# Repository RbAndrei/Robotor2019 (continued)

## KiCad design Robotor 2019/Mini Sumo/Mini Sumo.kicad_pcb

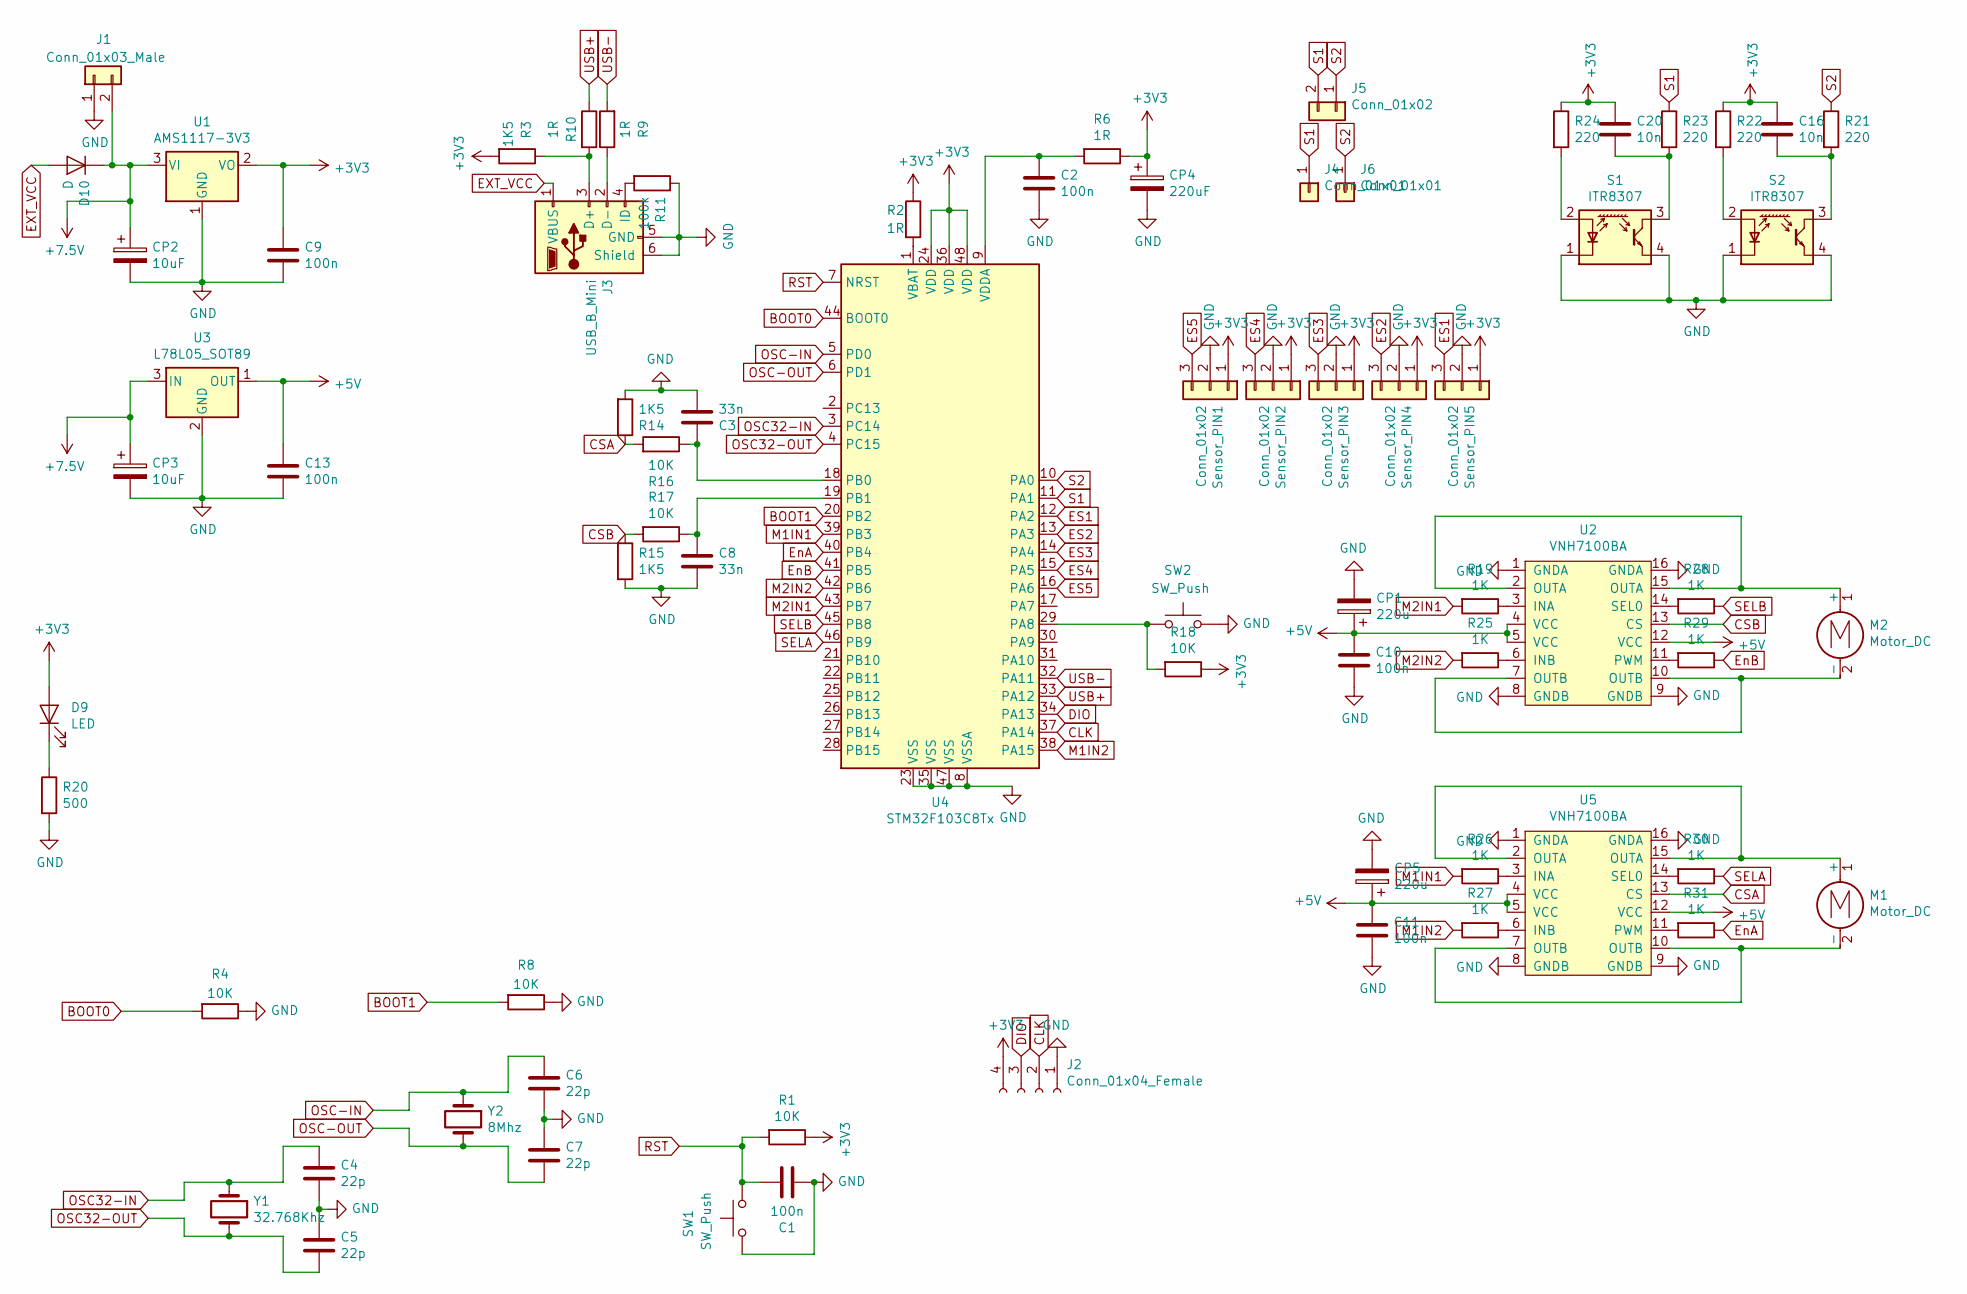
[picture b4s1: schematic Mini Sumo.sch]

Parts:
C1, C2, C9, C10, C11, C13: 100n; C_0805_2012Metric_Pad1.15x1.40mm_HandSolder
C3, C8: 33n; C_0805_2012Metric_Pad1.15x1.40mm_HandSolder
C4, C5, C6, C7: 22p; C_0805_2012Metric_Pad1.15x1.40mm_HandSolder
C16, C20: 10n; C_0805_2012Metric_Pad1.15x1.40mm_HandSolder
CP1, CP5: 220u; CP_Elec_4x5.3
CP2, CP3: 10uF; CP_Elec_4x5.3
CP4: 220uF; CP_Elec_4x5.3
D9: LED; LED_0805_2012Metric_Pad1.15x1.40mm_HandSolder
D10: D; D_A-405_P5.08mm_Vertical_AnodeUp
J1: Conn_01x03_Male; PinSocket_1x02_P2.54mm_Vertical
J2: Conn_01x04_Female; PinSocket_1x04_P2.54mm_Vertical
J3: USB_B_Mini; USB_Mini-B_Lumberg_2486_01_Horizontal
J4, J6: Conn_01x01; PinSocket_1x01_P2.54mm_Vertical
J5: Conn_01x02; PinSocket_1x02_P2.54mm_Vertical
M1, M2: Motor_DC; SolderWirePad_1x02_P5.08mm_Drill1.5mm
R1, R4, R8, R16, R17, R18: 10K; R_0805_2012Metric_Pad1.15x1.40mm_HandSolder
R2, R6, R9, R10: 1R; R_0805_2012Metric_Pad1.15x1.40mm_HandSolder
R3, R14, R15: 1K5; R_0805_2012Metric_Pad1.15x1.40mm_HandSolder
R11: 100k; R_0805_2012Metric_Pad1.15x1.40mm_HandSolder
R19, R25, R26, R27, R28, R29, R30, R31: 1K; R_0805_2012Metric_Pad1.15x1.40mm_HandSolder
R20: 500; R_0805_2012Metric_Pad1.15x1.40mm_HandSolder
R21, R23: 220; R_0805_2012Metric_Pad1.15x1.40mm_HandSolder
R22, R24: 220; R_1206_3216Metric_Pad1.42x1.75mm_HandSolder
S1, S2: ITR8307; Everlight_ITR8307
SW1, SW2: SW_Push; SW_SPST_CK_RS282G05A3
Sensor_PIN1, Sensor_PIN2, Sensor_PIN3, Sensor_PIN4, Sensor_PIN5: Conn_01x02; PinSocket_1x03_P2.54mm_Vertical
U1: AMS1117-3V3; SOT-223-3_TabPin2
U2, U5: VNH7100BA; SOIC-16_3.9x9.9mm_P1.27mm
U3: L78L05_SOT89; SOT-89-3_Handsoldering
U4: STM32F103C8Tx; LQFP-48_7x7mm_P0.5mm
Y1: 32.768Khz; Crystal_SMD_0603-2Pin_6.0x3.5mm_HandSoldering
Y2: 8Mhz; Crystal_SMD_SeikoEpson_MA505-2Pin_12.7x5.1mm

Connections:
+3V3: C9.1, C16.1, C20.1, CP4.1, D9.2 (A), J2.4, R1.1, R2.1, R3.2, R6.1, R18.1, R22.1, R24.1, Sensor_PIN1.1, Sensor_PIN2.1, Sensor_PIN3.1, Sensor_PIN4.1, Sensor_PIN5.1, U1.2 (VO), U4.24 (VDD), U4.36 (VDD), U4.48 (VDD)
+5V: C10.2, C11.2, C13.1, CP1.1, CP5.1, U2.4 (VCC), U2.5 (VCC), U2.12 (VCC), U3.1 (OUT), U5.4 (VCC), U5.5 (VCC), U5.12 (VCC)
+7.5V: CP2.1, CP3.1, D10.1 (K), J1.2, U1.3 (VI), U3.3 (IN)
BOOT0: R4.2, U4.44 (BOOT0)
BOOT1: R8.2, U4.20 (PB2)
CLK: J2.2, U4.37 (PA14)
CSA: R14.1, R16.2, U5.13 (CS)
CSB: R15.1, R17.2, U2.13 (CS)
DIO: J2.3, U4.34 (PA13)
ES1: Sensor_PIN5.3, U4.12 (PA2)
ES2: Sensor_PIN4.3, U4.13 (PA3)
ES3: Sensor_PIN3.3, U4.14 (PA4)
ES4: Sensor_PIN2.3, U4.15 (PA5)
ES5: Sensor_PIN1.3, U4.16 (PA6)
EXT_VCC: D10.2 (A), J3.1 (VBUS)
EnA: R31.1, U4.40 (PB4)
EnB: R29.1, U4.41 (PB5)
GND: C1.1, C2.2, C3.2, C4.2, C5.1, C6.2, C7.1, C8.2, C9.2, C10.1, C11.1, C13.2, CP1.2, CP2.2, CP3.2, CP4.2, CP5.2, J1.1, J2.1, J3.5 (GND), J3.6 (Shield), R4.1, R8.1, R11.1, R14.2, R15.2, R20.2, S1.1 (K), S1.4 (E), S2.1 (K), S2.4 (E), SW1.1, SW2.2, Sensor_PIN1.2, Sensor_PIN2.2, Sensor_PIN3.2, Sensor_PIN4.2, Sensor_PIN5.2, U1.1 (GND), U2.1 (GNDA), U2.8 (GNDB), U2.9 (GNDB), U2.16 (GNDA), U3.2 (GND), U4.8 (VSSA), U4.23 (VSS), U4.35 (VSS), U4.47 (VSS), U5.1 (GNDA), U5.8 (GNDB), U5.9 (GNDB), U5.16 (GNDA)
M1IN1: R26.2, U4.39 (PB3)
M1IN2: R27.2, U4.38 (PA15)
M2IN1: R19.2, U4.43 (PB7)
M2IN2: R25.2, U4.42 (PB6)
unnamed: C2.1, R6.2, U4.9 (VDDA)
unnamed: C3.1, R16.1, U4.18 (PB0)
unnamed: C8.1, R17.1, U4.19 (PB1)
unnamed: C16.2, R21.2, S2.3 (C)
unnamed: C20.2, R23.2, S1.3 (C)
unnamed: D9.1 (K), R20.1
unnamed: J3.2 (D-), R9.1
unnamed: J3.3 (D+), R3.1, R10.2
unnamed: J3.4 (ID), R11.2
unnamed: M1.1 (+), U5.2 (OUTA), U5.15 (OUTA)
unnamed: M1.2 (-), U5.7 (OUTB), U5.10 (OUTB)
unnamed: M2.1 (+), U2.2 (OUTA), U2.15 (OUTA)
unnamed: M2.2 (-), U2.7 (OUTB), U2.10 (OUTB)
unnamed: R2.2, U4.1 (VBAT)
unnamed: R18.2, SW2.1, U4.29 (PA8)
unnamed: R19.1, U2.3 (INA)
unnamed: R22.2, S2.2 (A)
unnamed: R24.2, S1.2 (A)
unnamed: R25.1, U2.6 (INB)
unnamed: R26.1, U5.3 (INA)
unnamed: R27.1, U5.6 (INB)
unnamed: R28.2, U2.14 (SEL0)
unnamed: R29.2, U2.11 (PWM)
unnamed: R30.2, U5.14 (SEL0)
unnamed: R31.2, U5.11 (PWM)
OSC32-IN: C4.1, U4.3 (PC14), Y1.1
OSC32-OUT: C5.2, U4.4 (PC15), Y1.2
OSC-IN: C6.1, U4.5 (PD0), Y2.1
OSC-OUT: C7.2, U4.6 (PD1), Y2.2
RST: C1.2, R1.2, SW1.2, U4.7 (NRST)
S1: J4.1, J5.2, R23.1, U4.11 (PA1)
S2: J5.1, J6.1, R21.1, U4.10 (PA0)
SELA: R30.1, U4.46 (PB9)
SELB: R28.1, U4.45 (PB8)
USB+: R10.1, U4.33 (PA12)
USB-: R9.2, U4.32 (PA11)

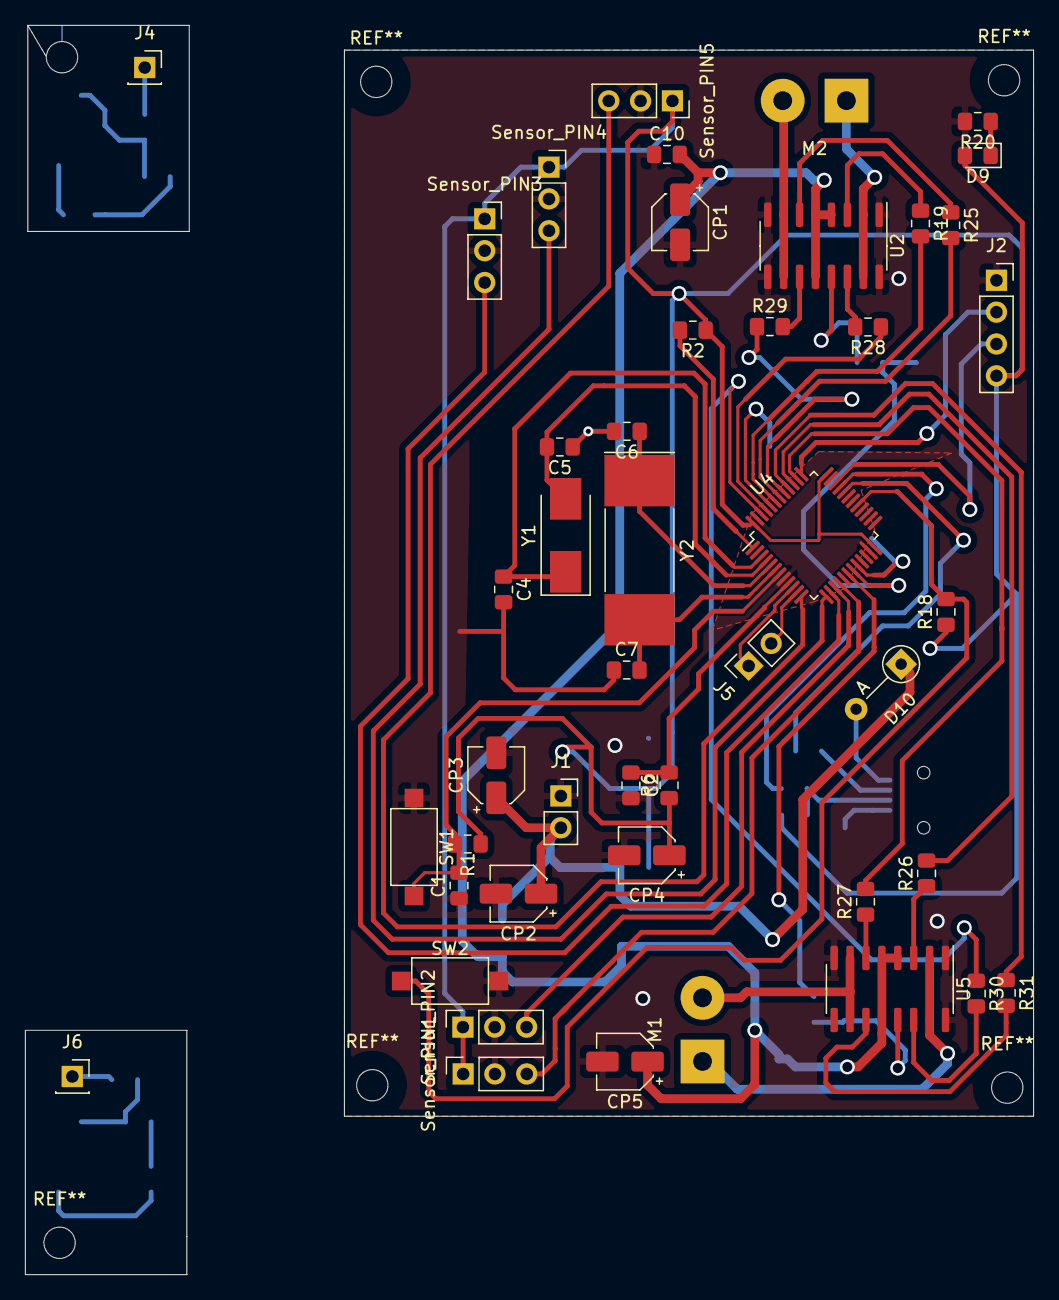
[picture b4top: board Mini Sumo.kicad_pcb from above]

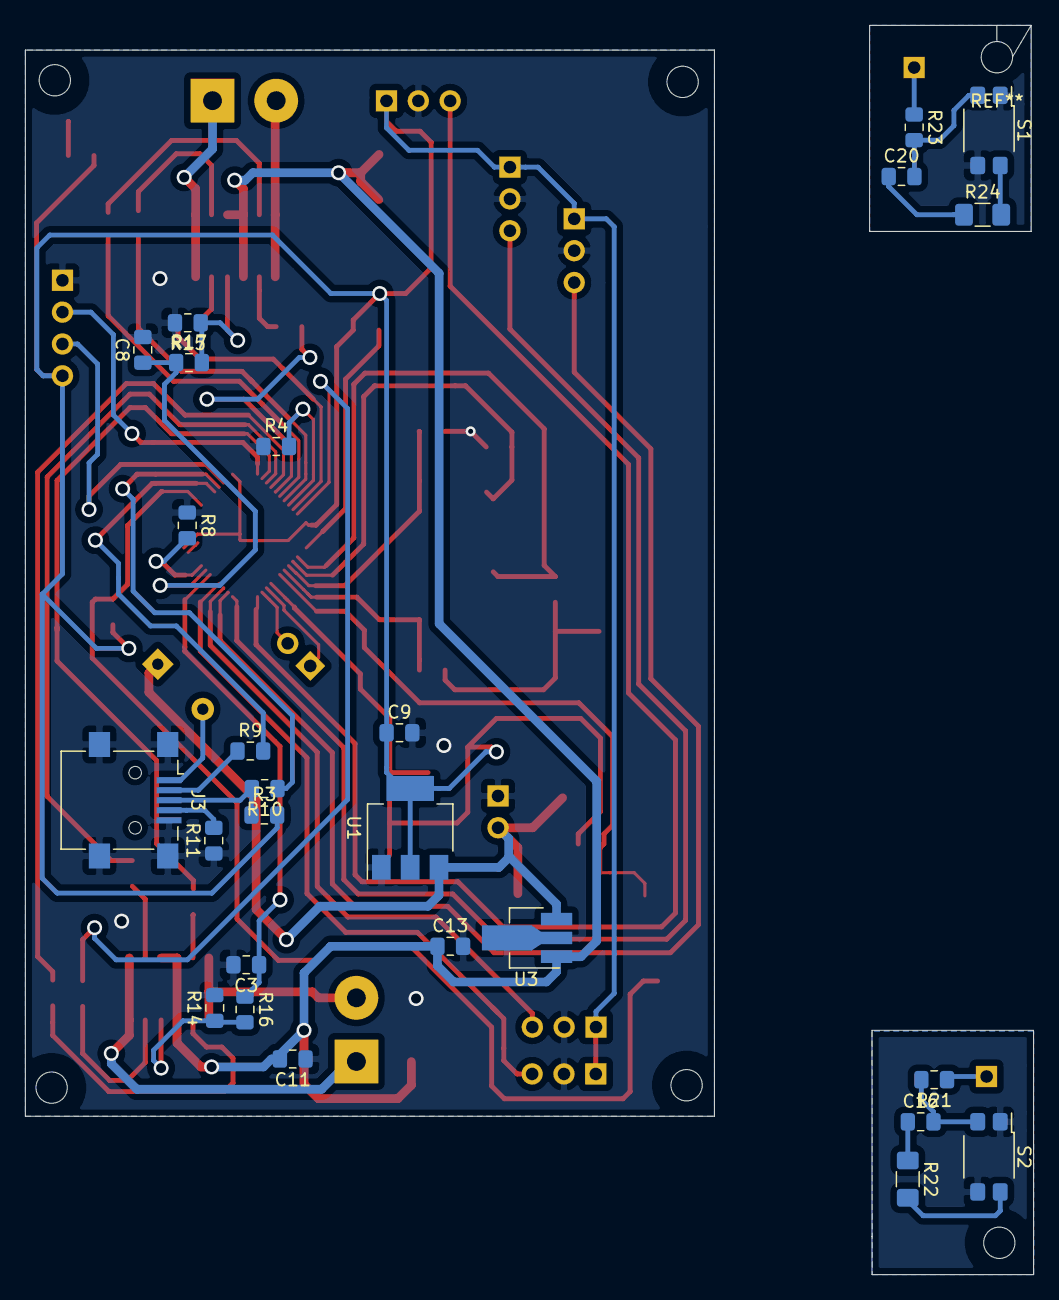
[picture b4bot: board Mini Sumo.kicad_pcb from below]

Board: 2 copper layers, 80.5 x 99.7 mm, 72 parts (26 on the bottom side), 58 nets.

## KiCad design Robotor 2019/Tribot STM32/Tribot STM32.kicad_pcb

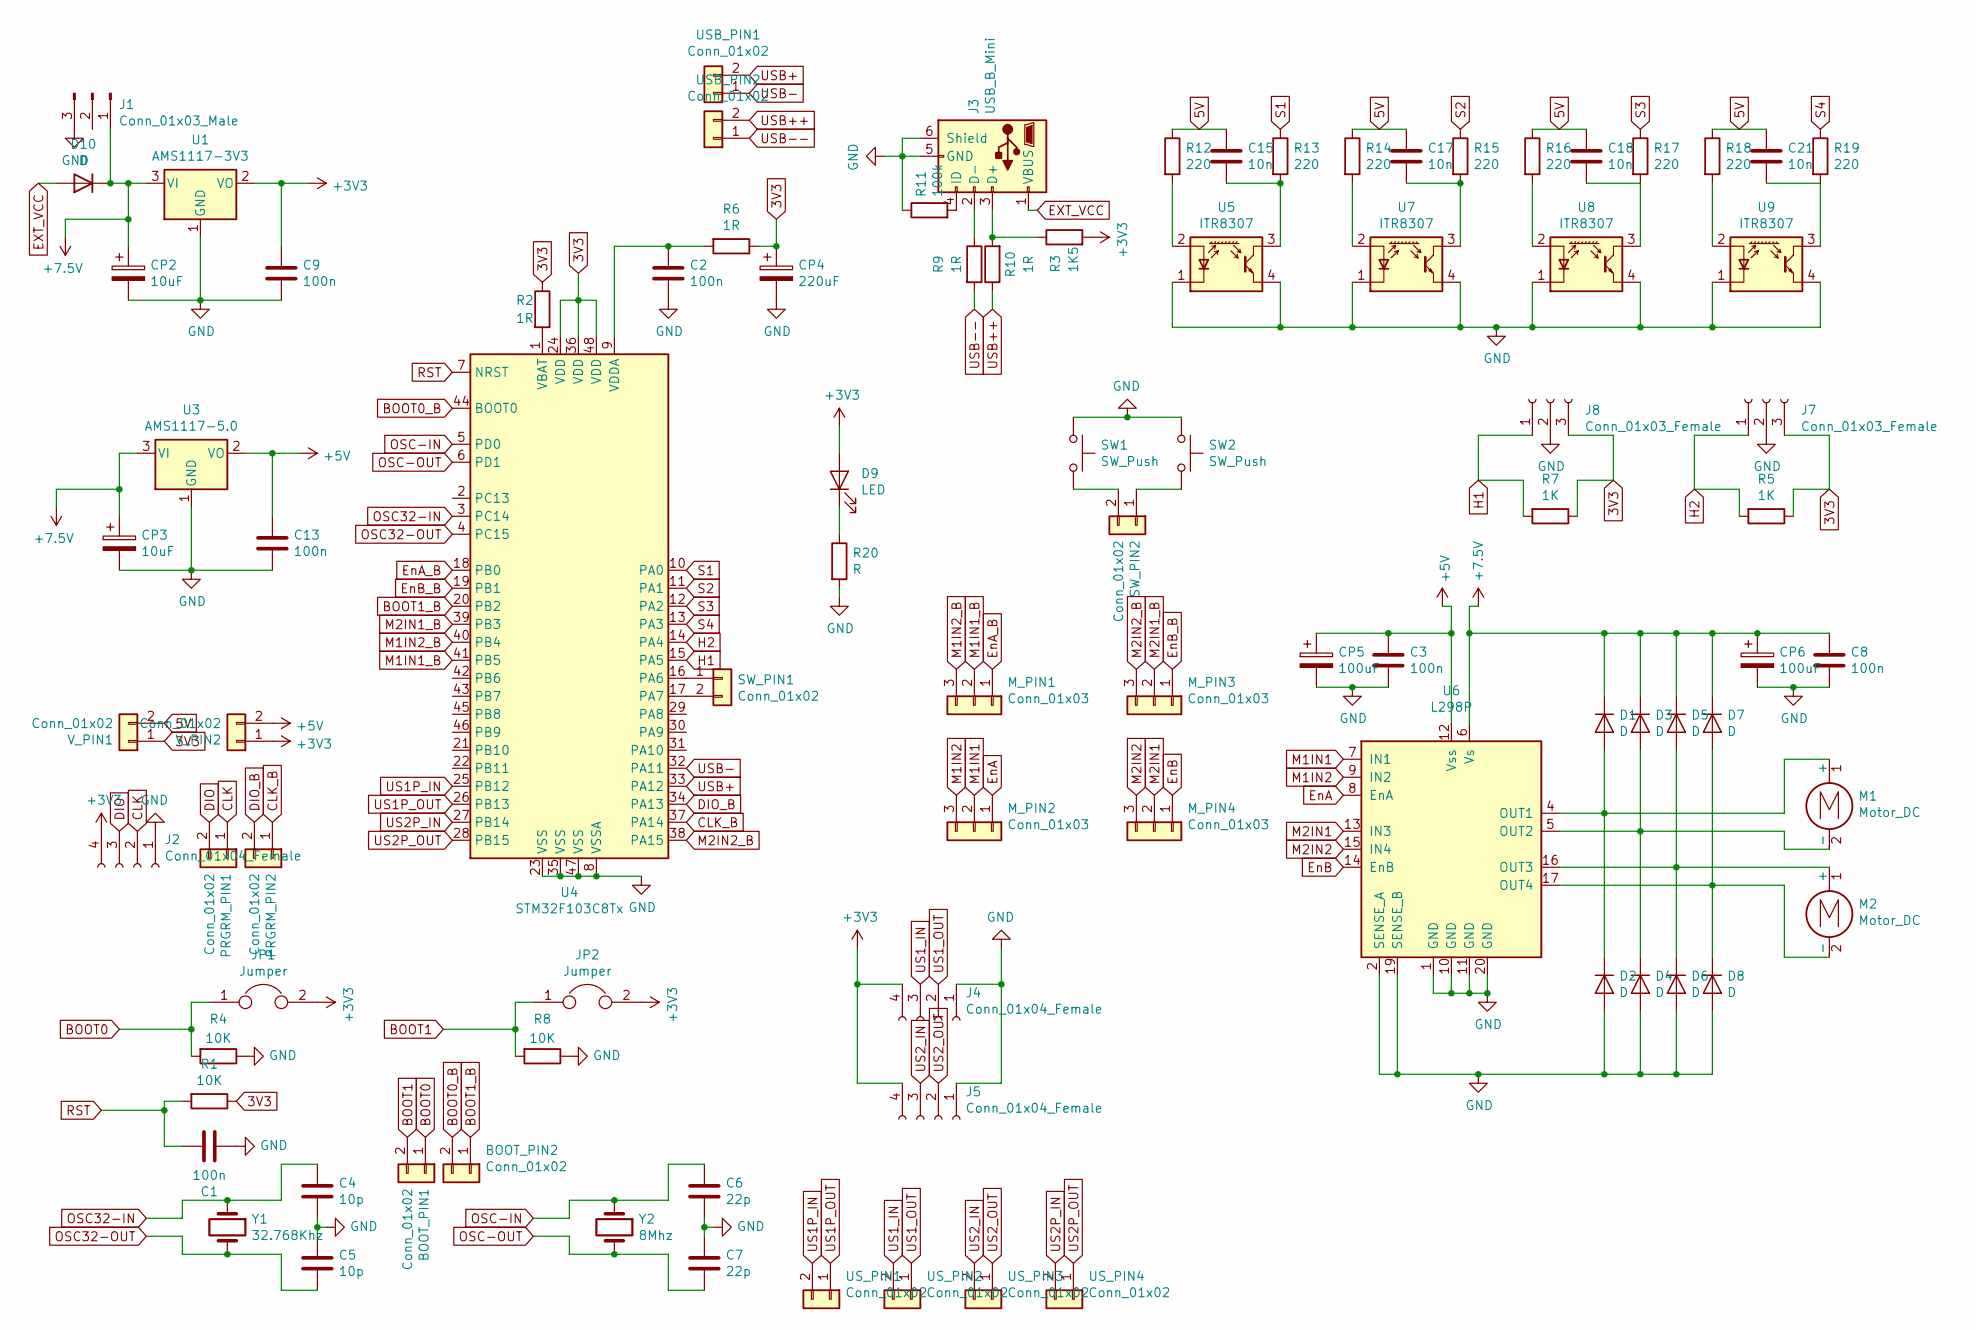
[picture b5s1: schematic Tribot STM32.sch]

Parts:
BOOT_PIN1, BOOT_PIN2: Conn_01x02; PinHeader_1x02_P2.54mm_Vertical
C1, C2, C3, C8, C9, C13: 100n; C_0805_2012Metric_Pad1.15x1.40mm_HandSolder
C4, C5: 10p; C_0805_2012Metric_Pad1.15x1.40mm_HandSolder
C6, C7: 22p; C_0805_2012Metric_Pad1.15x1.40mm_HandSolder
C15, C17, C18, C21: 10n; C_0805_2012Metric_Pad1.15x1.40mm_HandSolder
CP2, CP3: 10uF; CP_Elec_4x5.3
CP4: 220uF; CP_Elec_4x5.3
CP5, CP6: 100uF; CP_Elec_4x5.3
D1, D2, D3, D4, D5, D6, D7, D8, D10: D; D_A-405_P5.08mm_Vertical_AnodeUp
D9: LED; LED_0805_2012Metric_Pad1.15x1.40mm_HandSolder
J1: Conn_01x03_Male; SolderWirePad_1x03_P5.715mm_Drill2mm
J2: Conn_01x04_Female; PinSocket_1x04_P2.54mm_Vertical
J3: USB_B_Mini; USB_Mini-B_Lumberg_2486_01_Horizontal
J4, J5: Conn_01x04_Female; PinHeader_1x04_P2.54mm_Vertical
J7, J8: Conn_01x03_Female; PinHeader_1x03_P2.54mm_Vertical
JP1, JP2: Jumper; PinSocket_1x02_P2.54mm_Vertical
M1, M2: Motor_DC; SolderWirePad_1x02_P5.08mm_Drill1.5mm
M_PIN1, M_PIN2, M_PIN3, M_PIN4: Conn_01x03; PinSocket_1x03_P2.54mm_Vertical
PRGRM_PIN1, PRGRM_PIN2: Conn_01x02; PinHeader_1x02_P2.54mm_Vertical
R1, R4, R8: 10K; R_0805_2012Metric_Pad1.15x1.40mm_HandSolder
R2, R6, R9, R10: 1R; R_0805_2012Metric_Pad1.15x1.40mm_HandSolder
R3: 1K5; R_0805_2012Metric_Pad1.15x1.40mm_HandSolder
R5, R7: 1K; R_0805_2012Metric_Pad1.15x1.40mm_HandSolder
R11: 100k; R_0805_2012Metric_Pad1.15x1.40mm_HandSolder
R12, R13, R14, R15, R16, R17, R18, R19: 220; R_0805_2012Metric_Pad1.15x1.40mm_HandSolder
R20: R; R_0805_2012Metric_Pad1.15x1.40mm_HandSolder
SW1, SW2: SW_Push; SW_SPST_EVQPE1
SW_PIN1, SW_PIN2: Conn_01x02; PinSocket_1x02_P2.54mm_Vertical
U1: AMS1117-3V3; SOT-223-3_TabPin2
U3: AMS1117-5.0; SOT-223-3_TabPin2
U4: STM32F103C8Tx; LQFP-48_7x7mm_P0.5mm
U5, U7, U8, U9: ITR8307; Everlight_ITR8307
U6: L298P; HSOP-20-1EP_11.0x15.9mm_P1.27mm_SlugUp
USB_PIN1, USB_PIN2: Conn_01x02; PinHeader_1x02_P2.54mm_Vertical
US_PIN1, US_PIN2, US_PIN3, US_PIN4: Conn_01x02; PinHeader_1x02_P2.54mm_Vertical
V_PIN1, V_PIN2: Conn_01x02; SolderWirePad_1x02_P5.08mm_Drill1.5mm
Y1: 32.768Khz; Crystal_SMD_SeikoEpson_MA505-2Pin_12.7x5.1mm
Y2: 8Mhz; Crystal_SMD_SeikoEpson_MA505-2Pin_12.7x5.1mm

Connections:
3V3: CP4.1, J7.3, J8.3, R1.1, R2.1, R5.1, R6.1, R7.1, U4.24 (VDD), U4.36 (VDD), U4.48 (VDD), V_PIN1.1
5V: C15.1, C17.1, C18.1, C21.1, R12.1, R14.1, R16.1, R18.1, V_PIN1.2
+3V3: C9.1, D9.2 (A), J2.4, J4.4, J5.4, JP1.2, JP2.2, R3.2, U1.2 (VO), V_PIN2.1
+5V: C3.1, C13.1, CP5.1, U3.2 (VO), U6.12 (Vss), V_PIN2.2
+7.5V: C8.1, CP2.1, CP3.1, CP6.1, D1.1 (K), D3.1 (K), D5.1 (K), D7.1 (K), D10.2 (K), J1.1, U1.3 (VI), U3.3 (VI), U6.6 (Vs)
BOOT0: BOOT_PIN1.1, JP1.1, R4.2
BOOT0_B: BOOT_PIN2.2, U4.44 (BOOT0)
BOOT1: BOOT_PIN1.2, JP2.1, R8.2
BOOT1_B: BOOT_PIN2.1, U4.20 (PB2)
CLK: J2.2, PRGRM_PIN1.1
CLK_B: PRGRM_PIN2.1, U4.37 (PA14)
DIO: J2.3, PRGRM_PIN1.2
DIO_B: PRGRM_PIN2.2, U4.34 (PA13)
EXT_VCC: D10.1 (A), J3.1 (VBUS)
EnA: M_PIN2.1, U6.8 (EnA)
EnA_B: M_PIN1.1, U4.18 (PB0)
EnB: M_PIN4.1, U6.14 (EnB)
EnB_B: M_PIN3.1, U4.19 (PB1)
GND: C1.1, C2.2, C3.2, C4.2, C5.1, C6.2, C7.1, C8.2, C9.2, C13.2, CP2.2, CP3.2, CP4.2, CP5.2, CP6.2, D2.2 (A), D4.2 (A), D6.2 (A), D8.2 (A), J1.3, J2.1, J3.5 (GND), J3.6 (Shield), J4.1, J5.1, J7.2, J8.2, R4.1, R8.1, R11.1, R20.2, SW1.1, SW2.1, U1.1 (GND), U3.1 (GND), U4.8 (VSSA), U4.23 (VSS), U4.35 (VSS), U4.47 (VSS), U5.1 (K), U5.4 (E), U6.1 (GND), U6.2 (SENSE_A), U6.10 (GND), U6.11 (GND), U6.19 (SENSE_B), U6.20 (GND), U7.1 (K), U7.4 (E), U8.1 (K), U8.4 (E), U9.1 (K), U9.4 (E)
H1: J8.1, R7.2, U4.15 (PA5)
H2: J7.1, R5.2, U4.14 (PA4)
M1IN1: M_PIN2.2, U6.7 (IN1)
M1IN1_B: M_PIN1.2, U4.41 (PB5)
M1IN2: M_PIN2.3, U6.9 (IN2)
M1IN2_B: M_PIN1.3, U4.40 (PB4)
M2IN1: M_PIN4.2, U6.13 (IN3)
M2IN1_B: M_PIN3.2, U4.39 (PB3)
M2IN2: M_PIN4.3, U6.15 (IN4)
M2IN2_B: M_PIN3.3, U4.38 (PA15)
unnamed: C2.1, R6.2, U4.9 (VDDA)
unnamed: C15.2, R13.2, U5.3 (C)
unnamed: C17.2, R15.2, U7.3 (C)
unnamed: C18.2, R17.2, U8.3 (C)
unnamed: C21.2, R19.2, U9.3 (C)
unnamed: D1.2 (A), D2.1 (K), M1.1 (+), U6.4 (OUT1)
unnamed: D3.2 (A), D4.1 (K), M1.2 (-), U6.5 (OUT2)
unnamed: D5.2 (A), D6.1 (K), M2.1 (+), U6.16 (OUT3)
unnamed: D7.2 (A), D8.1 (K), M2.2 (-), U6.17 (OUT4)
unnamed: D9.1 (K), R20.1
unnamed: J3.2 (D-), R9.1
unnamed: J3.3 (D+), R3.1, R10.2
unnamed: J3.4 (ID), R11.2
unnamed: R2.2, U4.1 (VBAT)
unnamed: R12.2, U5.2 (A)
unnamed: R14.2, U7.2 (A)
unnamed: R16.2, U8.2 (A)
unnamed: R18.2, U9.2 (A)
unnamed: SW1.2, SW_PIN2.2
unnamed: SW2.2, SW_PIN2.1
unnamed: SW_PIN1.1, U4.16 (PA6)
unnamed: SW_PIN1.2, U4.17 (PA7)
OSC32-IN: C4.1, U4.3 (PC14), Y1.1
OSC32-OUT: C5.2, U4.4 (PC15), Y1.2
OSC-IN: C6.1, U4.5 (PD0), Y2.1
OSC-OUT: C7.2, U4.6 (PD1), Y2.2
RST: C1.2, R1.2, U4.7 (NRST)
S1: R13.1, U4.10 (PA0)
S2: R15.1, U4.11 (PA1)
S3: R17.1, U4.12 (PA2)
S4: R19.1, U4.13 (PA3)
US1P_IN: U4.25 (PB12), US_PIN1.2
US1P_OUT: U4.26 (PB13), US_PIN1.1
US1_IN: J4.3, US_PIN2.2
US1_OUT: J4.2, US_PIN2.1
US2P_IN: U4.27 (PB14), US_PIN4.2
US2P_OUT: U4.28 (PB15), US_PIN4.1
US2_IN: J5.3, US_PIN3.2
US2_OUT: J5.2, US_PIN3.1
USB+: U4.33 (PA12), USB_PIN1.2
USB++: R10.1, USB_PIN2.2
USB-: U4.32 (PA11), USB_PIN1.1
USB--: R9.2, USB_PIN2.1

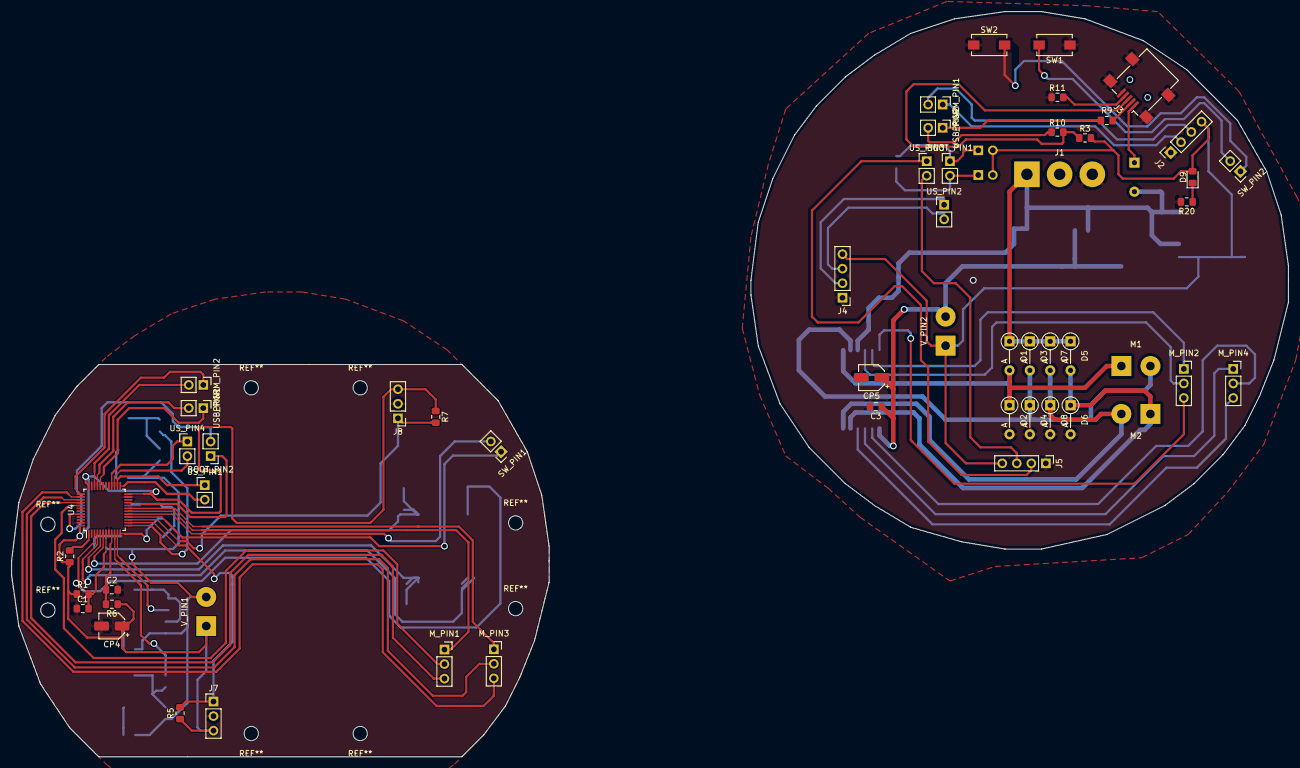
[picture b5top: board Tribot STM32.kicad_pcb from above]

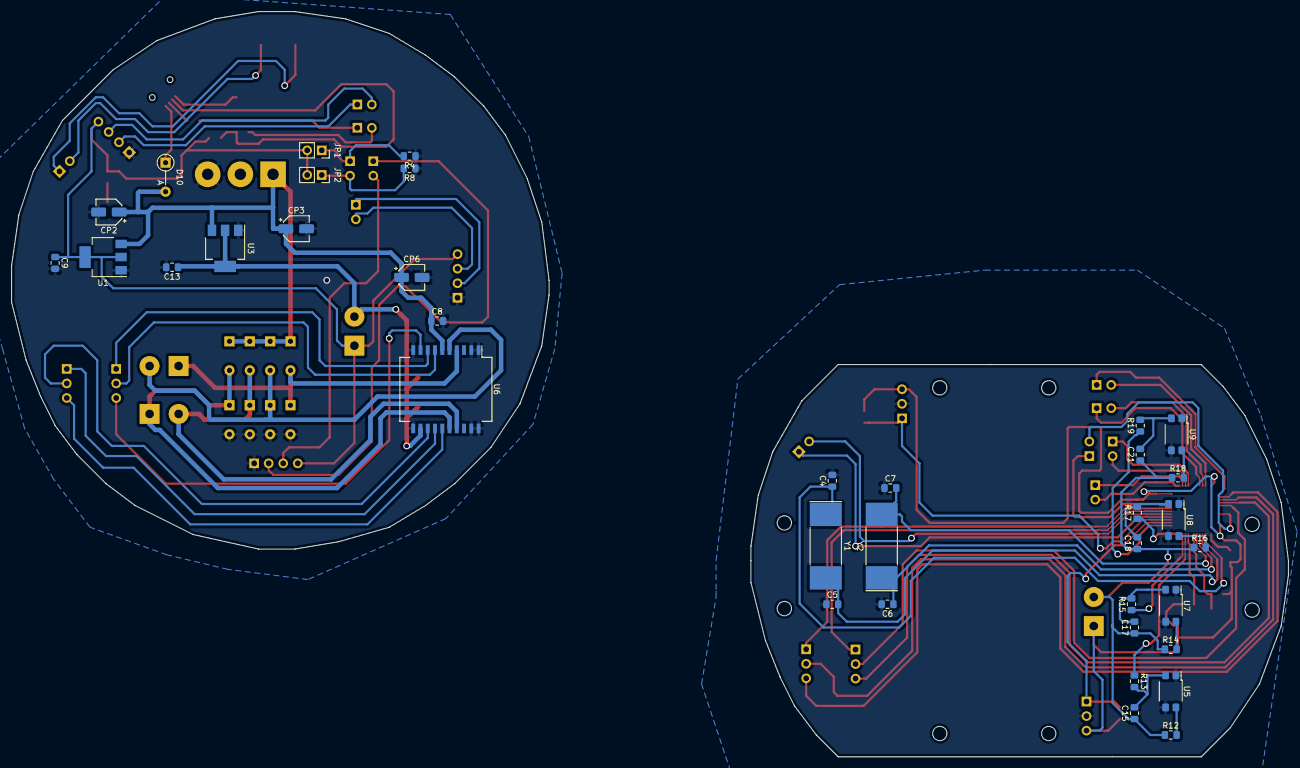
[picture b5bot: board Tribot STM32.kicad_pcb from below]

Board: 2 copper layers, 223.3 x 130.3 mm, 90 parts (36 on the bottom side), 72 nets.

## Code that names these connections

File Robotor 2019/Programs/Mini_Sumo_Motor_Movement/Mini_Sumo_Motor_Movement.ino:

#define ENB PB5
#define SELB PB8
#define M2IN1 PB6
#define M2IN2 PB7

#define Button PA8

#define ENA PC13
#define SELA PB9
#define M1IN1 PA9
#define M1IN2 PA10

#define S1 PA1
#define S2 PA0

#define ES1 PA2
#define ES2 PA3
#define ES3 PA4
#define ES4 PA5
#define ES5 PA6

void setup() {
  // put your setup code here, to run once:
  pinMode(ENB, OUTPUT);
  pinMode(SELB, OUTPUT);
  pinMode(M2IN1, OUTPUT);
  pinMode(M2IN2, OUTPUT);

  pinMode(ENA, OUTPUT);
  pinMode(SELA, OUTPUT);
  pinMode(M1IN1, OUTPUT);
  pinMode(M2IN2, OUTPUT);
    
  pinMode(Button, INPUT_PULLUP);

  pinMode(S1, INPUT);
  pinMode(S2, INPUT);
  pinMode(ES1, INPUT);
  pinMode(ES2, INPUT);
  pinMode(ES3, INPUT);
  pinMode(ES4, INPUT);
  pinMode(ES5, INPUT);
}

int lastButtonState = digitalRead(Button);
int buttonState = 0;
int idleState = 1;

  int value1 = analogRead(S1);
  int value2 = analogRead(S2);
  int distancevalue1 = digitalRead(ES1);
  int distancevalue2 = digitalRead(ES2);
  int distancevalue3 = digitalRead(ES3);
  int distancevalue4 = digitalRead(ES4);
  int dsitancevalue5 = digitalRead(ES5);

void loop() {
  // put your main code here, to run repeatedly:
  Start();

  value1 = analogRead(S1);
  value2 = analogRead(S2);
  distancevalue1 = digitalRead(ES1);
  distancevalue2 = digitalRead(ES2);
  distancevalue3 = digitalRead(ES3);
  distancevalue4 = digitalRead(ES4);
  dsitancevalue5 = digitalRead(ES5);

    digitalWrite(ENB, HIGH);
    analogWrite(M2IN1, 100);
    analogWrite(M2IN2, 0);

    digitalWrite(ENA, HIGH);
    analogWrite(M1IN1, 255);
    analogWrite(M1IN2, 0);
}

void Start(void){
  buttonState = digitalRead(Button);
  
  if(buttonState != lastButtonState){
    if(buttonState == LOW)
       idleState = !idleState;
     delay(50);
    lastButtonState = buttonState;
  }
}

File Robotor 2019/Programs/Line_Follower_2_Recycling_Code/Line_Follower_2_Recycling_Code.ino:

#include<math.h>

#define LED1 PB11
#define LED2 PB10
#define Button PB9 /*  Se creeaza valori carora le alocam pini, aceeiasi chestie cu "int Button = 13;"*/
#define AIN2 PB6 /* Fiecare variabila careia i se atribuie o valoare in afara unei functii, valoarea ei este considerata ca fiind numarul pinului */ 
#define AIN1 PB7
#define BIN2 PA10  // intrarile de la motoare
#define BIN1 PA9 
#define ENA PB5  //seteaza viteza motoarelor
#define ENB PC13
#define digitalSensor PB8


int sensor[10] = {PA0, PA1, PA2, PA3, PA4, PA5, PA6, PA7, PB0, PB1}; /* Desemnam pinii sensorilor de pe Arduino, pot fi notati fi cu A0-A7 fie cu 18-25, au si alte notatii */

float speedA = 0; /* Deoarece nu exista pinul 0 pe Arduino, incep de la 1, variabilelor le poate fi data valoarea 0, nefiind considerat pin */
float speedB = 0;


int buttonState = 0;
int lastbuttonState = 0;
int x = 0;
float d = 0;
float d2 = 0;
float d3 = 0;
double kp = 0;
double kd = 0;
double ki = 0;
int Speed = 0;
int index1[11];
int s[10];
int valori[10];
int curba0 = 0;
int curba = 0;
int curba2 = 0;
int curba3 = 0;
int curba4 = 0;

void setup() {
  pinMode(digitalSensor, INPUT);
  pinMode(LED1, OUTPUT);
  pinMode(LED2, OUTPUT);
  pinMode(AIN1, OUTPUT);
  pinMode(AIN2, OUTPUT);
  pinMode(BIN1, OUTPUT);
  pinMode(BIN2, OUTPUT);
  pinMode(ENA, OUTPUT);
  pinMode(ENB, OUTPUT);
  pinMode(Button, INPUT_PULLUP);/* "INPUT_PULLUP" desemneaza pinul ca fiind de input si il seteaza ca fiind "HIGH" */
  lastbuttonState = digitalRead(Button);
  for(int i = 0; i<10; i++)
    pinMode(sensor[i], INPUT_ANALOG);

  digitalWrite(LED1, HIGH);
  
  Serial.begin(9600);
}

void loop() {


for(int i = 0; i<10; i++){
  s[i] = analogRead(sensor[i]); /* Citim valorile sensorilor si le punem intr-un vecctor */
  delay(1); /* Delay de 1 milisecunda penru stabilitate */
}

    kp = 30;
    kd = 100;
    ki = 0.02;
    curba0 = 10;
    curba = 15;
    curba2 = 20;
    curba3 = 25;
    curba4 = 30;

  
  d2 = d;
  d = error();
  
  //Serial.print(d); Serial.print(" ");Serial.print(d2);Serial.println(" ");
  if(isnan(d))
    d = d2;

  if(digitalRead(digitalSensor) == 1 && d == 0)
    Speed = 300;
    else Speed = 150;

  if(abs(d) >= 3){
      Speed = 200;
      kp = 60;
      kd = 180;
      ki = 0.14;
      curba0 = 25;
      curba = 30;
      curba2 = 35;
      curba3 = 40;
      curba4 = 45;
    }else if(abs(d) >= 2){ 
      Speed = 180;
      kp = 50;
      kd = 150;
      ki = 0.09;
      curba2 = 10;
      curba3 = 15;
      curba4 = 20;
      }else{
        Speed = 160;
        kp = 40;
        kd = 120;
        ki = 0.05;
        curba0 = 20;
        curba = 25;
        curba2 = 30;
        }
  if(abs(d) >= 4)
    ki = 0.35;
   
   /* Formula de reglare PID */
   speedA = Speed + ((kp*d)+(kd*(d-d2))+(ki*(d+d2)));
   speedB = Speed - ((kp*d)+(kd*(d-d2))+(ki*(d+d2)));

   /* Daca valoare vitezei trece peste 255 atunci arduino o scade cu 255 si pune valoarea rezultata ca viteza motoarelor */
   
     if(abs(d) > 3){
       if(speedA < speedB)
         speedA -= curba4;
       else if(speedB < speedA)
         speedB -= curba4; 
     }
     else if(abs(d) > 2.5){
      if(speedA < speedB)
        speedA -= curba3;
      else if(speedB < speedA)
        speedB -= curba3;
     }else if(abs(d) > 2){
      if(speedA < speedB)
        speedA -= curba2;
      else if(speedB < speedA)
        speedB -= curba2;
     }else if(abs(d) > 1.5){
      if(speedA < speedB)
        speedA -= curba;
      else if(speedB < speedA)
        speedB -= curba;
     }else if(abs(d) > 1){
      if(speedA < speedB)
        speedA -= curba0;
      else if(speedB < speedA)
        speedB -= curba0;
     }
<<<<<<< HEAD
   if(speedA > 255)
      speedA = 255;
   if(speedB > 255)
      speedB = 255;
  
   if(speedA < -255)
      speedA = -255;
   if (speedB < -255)
      speedB = -255;
=======
>>>>>>> 7664a01938009c8ba603cac55e0d99415c4fcbd9
  //Serial.print(speedA); Serial.print(" "); Serial.println(speedB);
    
  Start();
  
  if(x == 1){
    if(speedB > 0){
      analogWrite(BIN2, abs(speedB));
      analogWrite(BIN1, 0);
      digitalWrite(ENB, HIGH);
    }
    else{
      analogWrite(BIN2, 0);
      analogWrite(BIN1, abs(speedB));
      digitalWrite(ENB, HIGH);
    }
 
    
    if(speedA < 0){
      analogWrite(AIN1, abs(speedA));
      analogWrite(AIN2, 0);
      digitalWrite(ENA, HIGH);
    }
    else{
      analogWrite(AIN1, 0);
      analogWrite(AIN2, abs(speedA));
      digitalWrite(ENA, HIGH);
    }
  }
  else {
    digitalWrite(ENB, LOW);
    digitalWrite(ENA, LOW);
  }
}



/* * * * * * * * * * * * * * * * * * * * * * * * * * * * * * * * * * * * * * * * * * * * * * * * * * * * * * * * */


void Start(void){
  /* Citim starea butonului si daca este diferita de starea anterioara si are valoarea "LOW" se seteaza x ca !x */
  buttonState = digitalRead(Button);
  digitalWrite(LED2, HIGH); 
    if (buttonState != lastbuttonState){
      if (buttonState == LOW){
        x = !x;
        if(x){
          //Calibrating();
          digitalWrite(LED2, LOW);
          delay(1000);
          //Serial.println(x);
        }
       }
     }
     /* Se updateaza valoarea anterioara */
     lastbuttonState = buttonState;
     
}
/*
void Calibrating(){
  int i=0;
  long int calibrationStartTime = millis();
  int sensorMax = 0;
  int sensorMin = 1023;
  while(millis() - calibrationStartTime < 5000){
      int sensorValue = analogRead(sensor[i]);
      if(sensorValue < sensorMin)
        sensorValues[i].MIN = sensorValue;
      else if(sensorValue > sensorMax)
        sensorValues[i].MAX = sensorValue;
      if(i<10)
      i++;
      else
      i=0;
  }
}
*/
void Finding(void){
  int n = 0;
  memset(index1, 0, sizeof(index1)); /* Seteaza toate valorile vectorului index1 cu valoarea celui de-al doilea parametru, 0 in cazul acesta */
  
  //memset(valori, 0, sizeof(valori));
  
  for(int i = 0; i < 10; i++){
    
    //Serial.print(s[i]); Serial.print(" "); Serial.print(i); Serial.print(" ");
    
    if(s[i] > 2500){ /* Daca valoarea citita de sensori este mai mare ca 2500 se memoreaza valoarea si indicele lui in vectorul valori, respectiv index1 */
      
      //valori[n] = s[i];
      //Serial.print(valori[n]); Serial.print(" ");
      
      index1[n] = i+1; /* Se retin pozitia + 1 pentru conditia de la "for" din functia "error" de sub, deoarece i incepe de la 0 */
      
      //Serial.print(index1[n]); Serial.print(" ");
      
      n++;
    }
  }
    //Serial.println();
}

float error(void){
    Finding();
    /* Se face media aritmetica a pozitiilor valorilor mai mari de 550 si se returneaza rezultatul minus 4.5, 
       deoarece aceia este mijlocul senzorului, intre pozitiile 4 si 5 */
    
    int n = 0;
    int sum = 0;
    float Ma = 0.0;
    for(int i = 0; index1[i] != 0 && i < 10; i++){
      sum += index1[i];
      n++;
      //Serial.print(index1[i]); Serial.print(" ");
    }
    //Serial.println();
    Ma = float(sum)/n;
    //Serial.print(Ma); Serial.print(" ");Serial.print(sum); Serial.print(" ");Serial.print(n); Serial.println(" ");
    return(Ma-5.5);   
}

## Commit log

2019-07-22 Initial commit.
    Schematic for solar-powered robot and tribot.
2019-07-22 Testing stuff
2019-07-23 Nici nu mai stiu, am facut la scoala pe data de 23.07
2019-07-23 Assigned footprints to all parts. Arranged sensors in PCB schematic.
2019-07-24 The PCB for Tribot up to the point we realised we need a 2nd floor.
2019-07-24 Line Follower Initial Commit
2019-07-24 Hopefully it works, Line Follower scheme added.
2019-07-25 Updated electric schematic for tribot with 2 floors.
2019-07-26 Bottom tribot circuit board.
2019-07-26 Tribot bottom circuit board final version (hopefully)
2019-07-26 Solar robot final circuit board (hopefully)
2019-07-27 Final solar robot pcb schematic (added mounting holes for motors and changed clearance on existing through-holes) Added all-red pdf printer file.
2019-07-27 Tidied up line follower eschema: - Moved components around. - Removed USB voltage regulator. - Added USB power output to battery voltage regulator.
    Annotated components in eschema, assigned footprints, created a netlist.
2019-07-27 Updated the readme for funsies.
2019-07-27 Added PCB board file.
2019-08-08 Tweaked PCB track widths. Added compnent values in both eschemas. Printed Front and Back tracks and a parts list to PDF.
2019-08-08 Line Follower robot electric schematic and PCB.
2019-08-08 Yeah I need to add a git ignore for most of this stuff
2019-08-08 Small tweaks to vias, paths, added parts lists.
2019-08-09 Just like 2 damn tracks, nothing important, everything still seems to work.
2019-08-21 Programele de azi
2019-08-21 no message
2019-08-21 Am uitat sa sterg astea
2019-08-21 Changed variables so I could check them in STM Studio
2019-08-25 Am copiat valorile de anul trecut. Momentan pare sa mearga destul de bine.
2019-08-29 Schemele nu au nicio schimbare, doar am miscat putin textul sa se vada bine la imprimanta.
    Programul am mai schimbat variabilele si vreau sa vad daca merge bine.
2019-08-31 Honestly I don't even remember
2019-09-01 Small changes
2019-09-01 First Entry of the Tribot Line Maze Program
2019-09-01 Slight changes to variable references and values
2019-09-01 Stuff from today
2019-09-02 Fecking Stuff
